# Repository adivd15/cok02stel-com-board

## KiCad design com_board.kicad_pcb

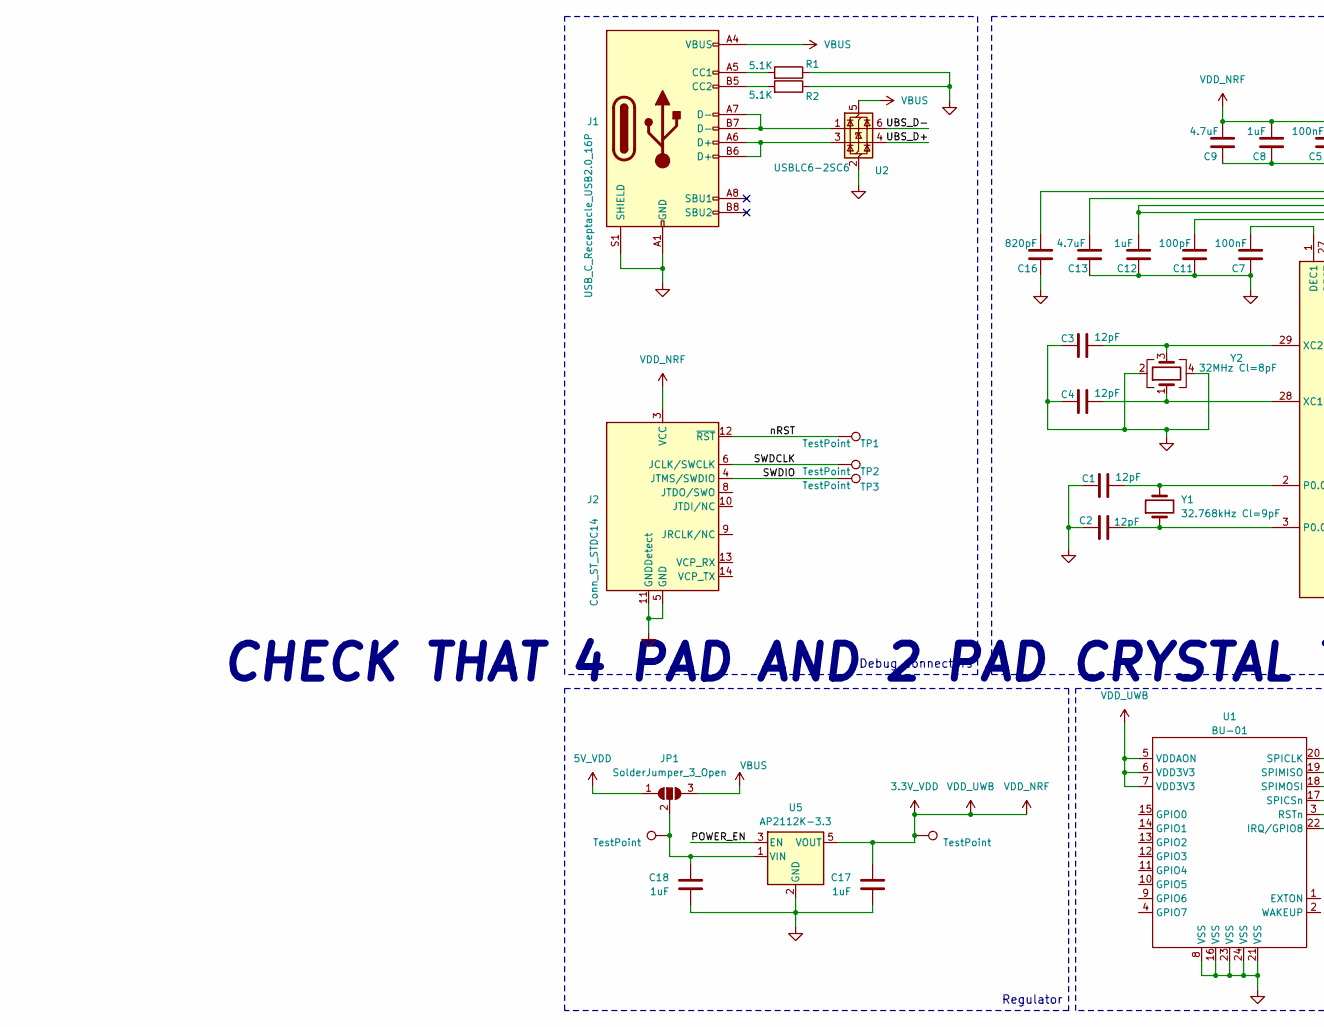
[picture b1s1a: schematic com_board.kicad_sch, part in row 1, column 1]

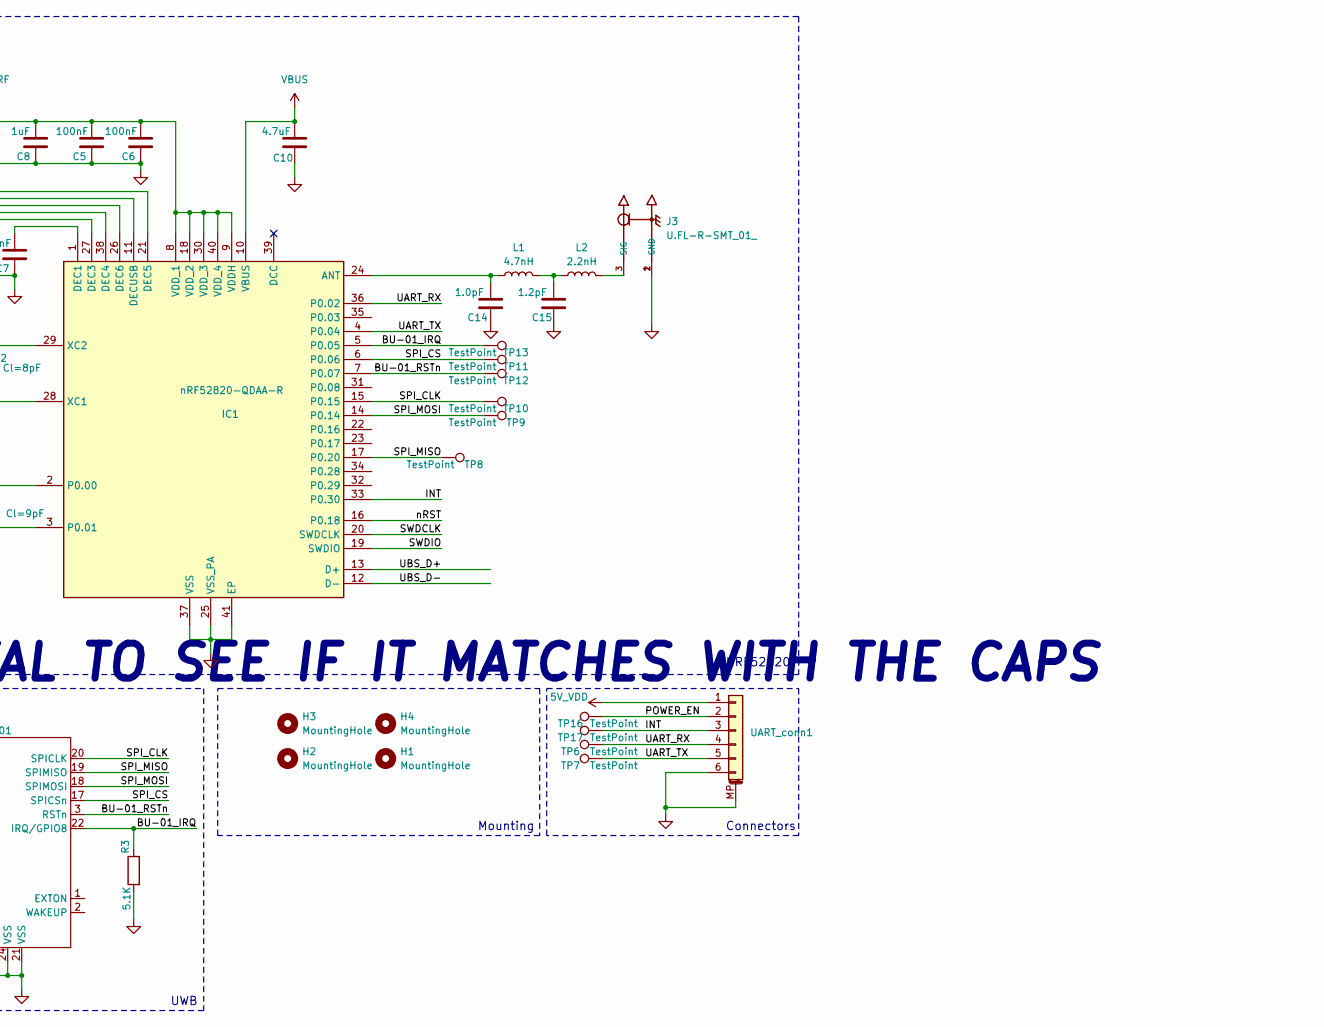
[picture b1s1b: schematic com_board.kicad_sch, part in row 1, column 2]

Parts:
C1, C2, C3, C4: 12pF; C_0201_0603Metric
C5, C6, C7: 100nF; C_0201_0603Metric
C8, C12, C17, C18: 1uF; C_0402_1005Metric_Pad0.74x0.62mm_HandSolder
C9, C10, C13: 4.7uF; C_0603_1608Metric_Pad1.08x0.95mm_HandSolder
C11: 100pF; C_0201_0603Metric
C14: 1.0pF; C_0201_0603Metric
C15: 1.2pF; C_0201_0603Metric
C16: 820pF; C_0201_0603Metric
H1, H2, H3, H4: MountingHole; MountingHole_2.2mm_M2
IC1: nRF52820-QDAA-R; QFN40P500X500X90-41N-D; Mouser Part Number 949-NRF52820-QDAA-R
J1: USB_C_Receptacle_USB2.0_16P; USB_C_Receptacle_GCT_USB4110
J2: Conn_ST_STDC14; PinHeader_2x07_P1.27mm_Vertical_SMD
J3: U.FL-R-SMT_01_; HRS_U.FL-R-SMT_01_
JP1: SolderJumper_3_Open; SolderJumper-3_P1.3mm_Open_Pad1.0x1.5mm_NumberLabels
L1: 4.7nH; L_0201_0603Metric_Pad0.64x0.40mm_HandSolder
L2: 2.2nH; L_0201_0603Metric_Pad0.64x0.40mm_HandSolder
R1, R2, R3: 5.1K; R_0402_1005Metric_Pad0.72x0.64mm_HandSolder
TP1, TP2, TP3, TP4, TP5, TP6, TP7, TP8, TP9, TP10, TP11, TP12, TP13, TP16, TP17: TestPoint; TestPoint_Pad_D1.0mm
U1: BU-01
U2: USBLC6-2SC6; SOT-23-6
U5: AP2112K-3.3; SOT-23-5
UART_conn1: FFC-FPC:TE_84952_6; TE_84952-6_1x06-1MP_P1.0mm_Horizontal
Y1: 32.768kHz Cl=9pF; Crystal_SMD_2012-2Pin_2.0x1.2mm_HandSoldering
Y2: 32MHz Cl=8pF; Crystal_SMD_2016-4Pin_2.0x1.6mm

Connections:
3.3V_VDD: C5.1, C6.1, C8.1, C9.1, C17.1, IC1.8 (VDD_1), IC1.9 (VDDH), IC1.18 (VDD_2), IC1.30 (VDD_3), IC1.40 (VDD_4), J2.3 (VCC), TP4.1, U1.5 (VDDAON), U1.6 (VDD3V3), U1.7 (VDD3V3), U5.5 (VOUT)
5V_VDD: JP1.1 (A), UART_conn1.1
/BU-01_IRQ: IC1.5 (P0.05), R3.1, TP13.1, U1.22 (IRQ/GPIO8)
/BU-01_RSTn: IC1.7 (P0.07), TP12.1, U1.3 (RSTn)
/INT: IC1.33 (P0.30), TP17.1, UART_conn1.3
/POWER_EN: TP16.1, U5.3 (EN), UART_conn1.2
/SPI_CLK: IC1.15 (P0.15), TP10.1, U1.20 (SPICLK)
/SPI_CS: IC1.6 (P0.06), TP11.1, U1.17 (SPICSn)
/SPI_MISO: IC1.17 (P0.20), TP8.1, U1.19 (SPIMISO)
/SPI_MOSI: IC1.14 (P0.14), TP9.1, U1.18 (SPIMOSI)
/SWDCLK: IC1.20 (SWDCLK), J2.6 (JCLK/SWCLK), TP2.1
/SWDIO: IC1.19 (SWDIO), J2.4 (JTMS/SWDIO), TP3.1
/UART_RX: IC1.36 (P0.02), TP6.1, UART_conn1.4
/UART_TX: IC1.4 (P0.04), TP7.1, UART_conn1.5
/UBS_D+: IC1.13 (D+), U2.4 (I/O2)
/UBS_D-: IC1.12 (D-), U2.6 (I/O1)
/nRST: IC1.16 (P0.18), J2.12 (~RST), TP1.1
GND: C1.2, C2.2, C3.2, C4.2, C5.2, C6.2, C7.2, C8.2, C9.2, C10.2, C11.2, C12.2, C13.2, C14.2, C15.2, C16.2, C17.2, C18.2, IC1.25 (VSS_PA), IC1.37 (VSS), IC1.41 (EP), J1.A1 (GND), J1.A12 (GND), J1.B1 (GND), J1.B12 (GND), J1.S1 (SHIELD), J2.5 (GND), J2.7 (GND), J2.11 (GNDDetect), J3.1 (GND), J3.2 (GND), R1.1, R2.1, R3.2, U1.8 (VSS), U1.16 (VSS), U1.21 (VSS), U1.23 (VSS), U1.24 (VSS), U2.2 (GND), U5.2 (GND), UART_conn1.6, UART_conn1.MP (MountPin), Y2.2, Y2.4
unnamed: C15.1, L1.2, L2.1
unnamed: C14.1, IC1.24 (ANT), L1.1
unnamed: C7.1, IC1.1 (DEC1)
unnamed: C11.1, IC1.27 (DEC3)
unnamed: C12.1, IC1.26 (DEC6), IC1.38 (DEC4)
unnamed: C16.1, IC1.21 (DEC5)
unnamed: C13.1, IC1.11 (DECUSB)
unnamed: C1.1, IC1.2 (P0.00), Y1.2
unnamed: C2.1, IC1.3 (P0.01), Y1.1
unnamed: C4.1, IC1.28 (XC1), Y2.1
unnamed: C3.1, IC1.29 (XC2), Y2.3
unnamed: J1.A5 (CC1), R1.2
unnamed: J1.B5 (CC2), R2.2
unnamed: J1.A6 (D+), J1.B6 (D+), U2.3 (I/O2)
unnamed: J1.A7 (D-), J1.B7 (D-), U2.1 (I/O1)
unnamed: J3.3 (SIG), L2.2
unnamed: C18.1, JP1.2 (C), TP5.1, U5.1 (VIN)
VBUS: C10.1, IC1.10 (VBUS), J1.A4 (VBUS), J1.A9 (VBUS), J1.B4 (VBUS), J1.B9 (VBUS), JP1.3 (B), U2.5 (VBUS)

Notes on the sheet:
UWB
NRF52820
Regulator
CHECK THAT 4 PAD AND 2 PAD CRYSTAL TO SEE IF IT MATCHES WITH THE CAPS
Connectors
Mounting
Debug connectors

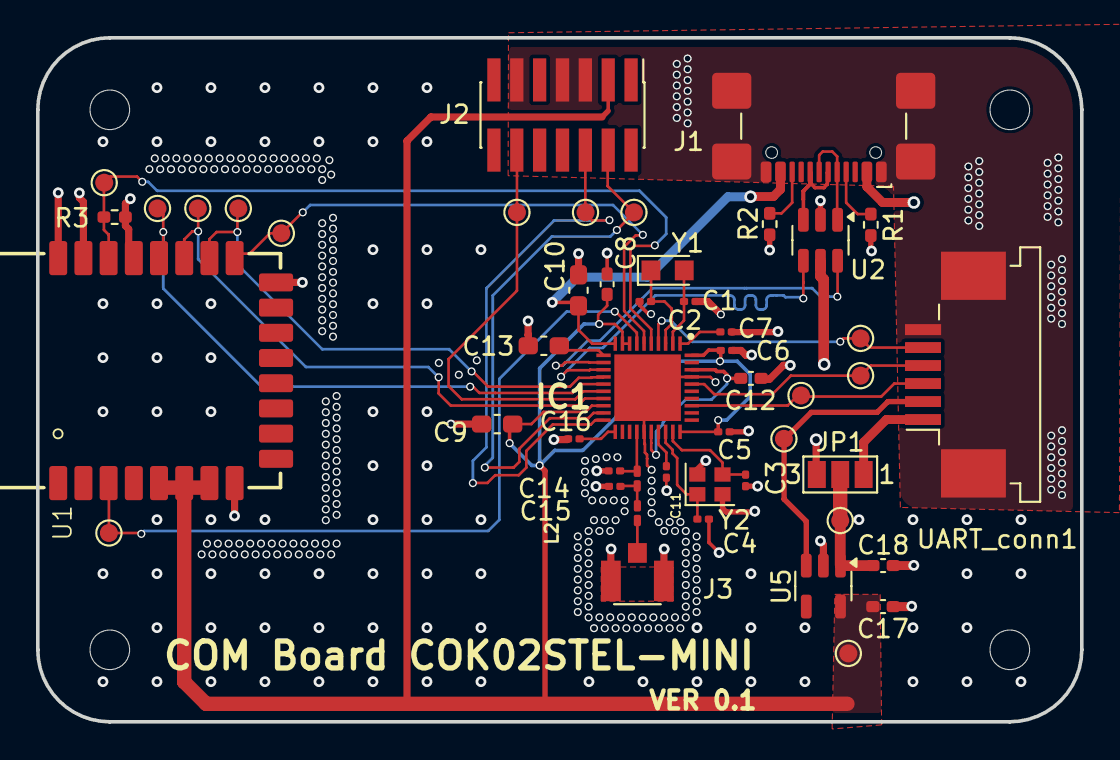
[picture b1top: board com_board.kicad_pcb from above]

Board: 4 copper layers, 58.0 x 38.0 mm, 53 parts (0 on the bottom side), 36 nets.

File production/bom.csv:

Designator,Footprint,Quantity,Value,LCSC Part #
"C1, C2, C3, C4",0201,4,12pF,
"C10, C13, C9",0603,3,4.7uF,
C11,0201,1,100pF,
"C12, C17, C18, C8",0402,4,1uF,
C14,0201,1,1.0pF,
C15,0201,1,1.2pF,
C16,0201,1,820pF,
"C5, C6, C7",0201,3,100nF,
IC1,QFN40P500X500X90-41N-D,1,nRF52820-QDAA-R,
J1,USB_C_Receptacle_GCT_USB4110,1,USB_C_Receptacle_USB2.0_16P,
J2,PinHeader_2x07_P1.27mm_Vertical_SMD,1,Conn_ST_STDC14,
J3,HRS_U.FL-R-SMT_01_,1,U.FL-R-SMT_01_,
L1,0201,1,4.7nH,
L2,0201,1,2.2nH,
"R1, R2, R3",0402,3,5.1K,
"TP1, TP10, TP11, TP12, TP13, TP16, TP17, TP2, TP3, TP4, TP5, TP6, TP7, TP8, TP9",TestPoint_Pad_D1.0mm,15,TestPoint,
U1,BU-01,1,BU-01,
U2,SOT-23-6,1,USBLC6-2SC6,
U5,SOT-23-5,1,AP2112K-3.3,
UART_CONN1,TE_84952-6_1x06-1MP_P1.0mm_Horizontal,1,FFC-FPC:TE_84952_6,
Y1,Crystal_SMD_2012-2Pin_2.0x1.2mm_HandSoldering,1,32.768kHz Cl=9pF,
Y2,Crystal_SMD_2016-4Pin_2.0x1.6mm,1,32MHz Cl=8pF,

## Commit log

2025-07-30 Added uwb module
2025-07-30 added libs to repo
2025-08-02 Finished schematic
2025-08-02 Fixed libs
2025-08-03 Almost done
2025-08-03 Worked on layou
2025-08-17 first iteration
2025-08-25 added name to pcb
